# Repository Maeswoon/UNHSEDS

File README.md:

# UNH SEDS

This is the official GitHub for UNH Students for the Exploration and Development of Space. 

Every September and February, UNH SEDS will train members on the software needed to use this. 
This GitHub is purely used for versioning engineering files at the moment, although an archive
of previous years' files is kept for posterity.

Please contact Mason McDonald at mason.mcdonald@unh.edu to join! 

Let's get to work,

Mason McDonald
<br>
*President, UNH SEDS*

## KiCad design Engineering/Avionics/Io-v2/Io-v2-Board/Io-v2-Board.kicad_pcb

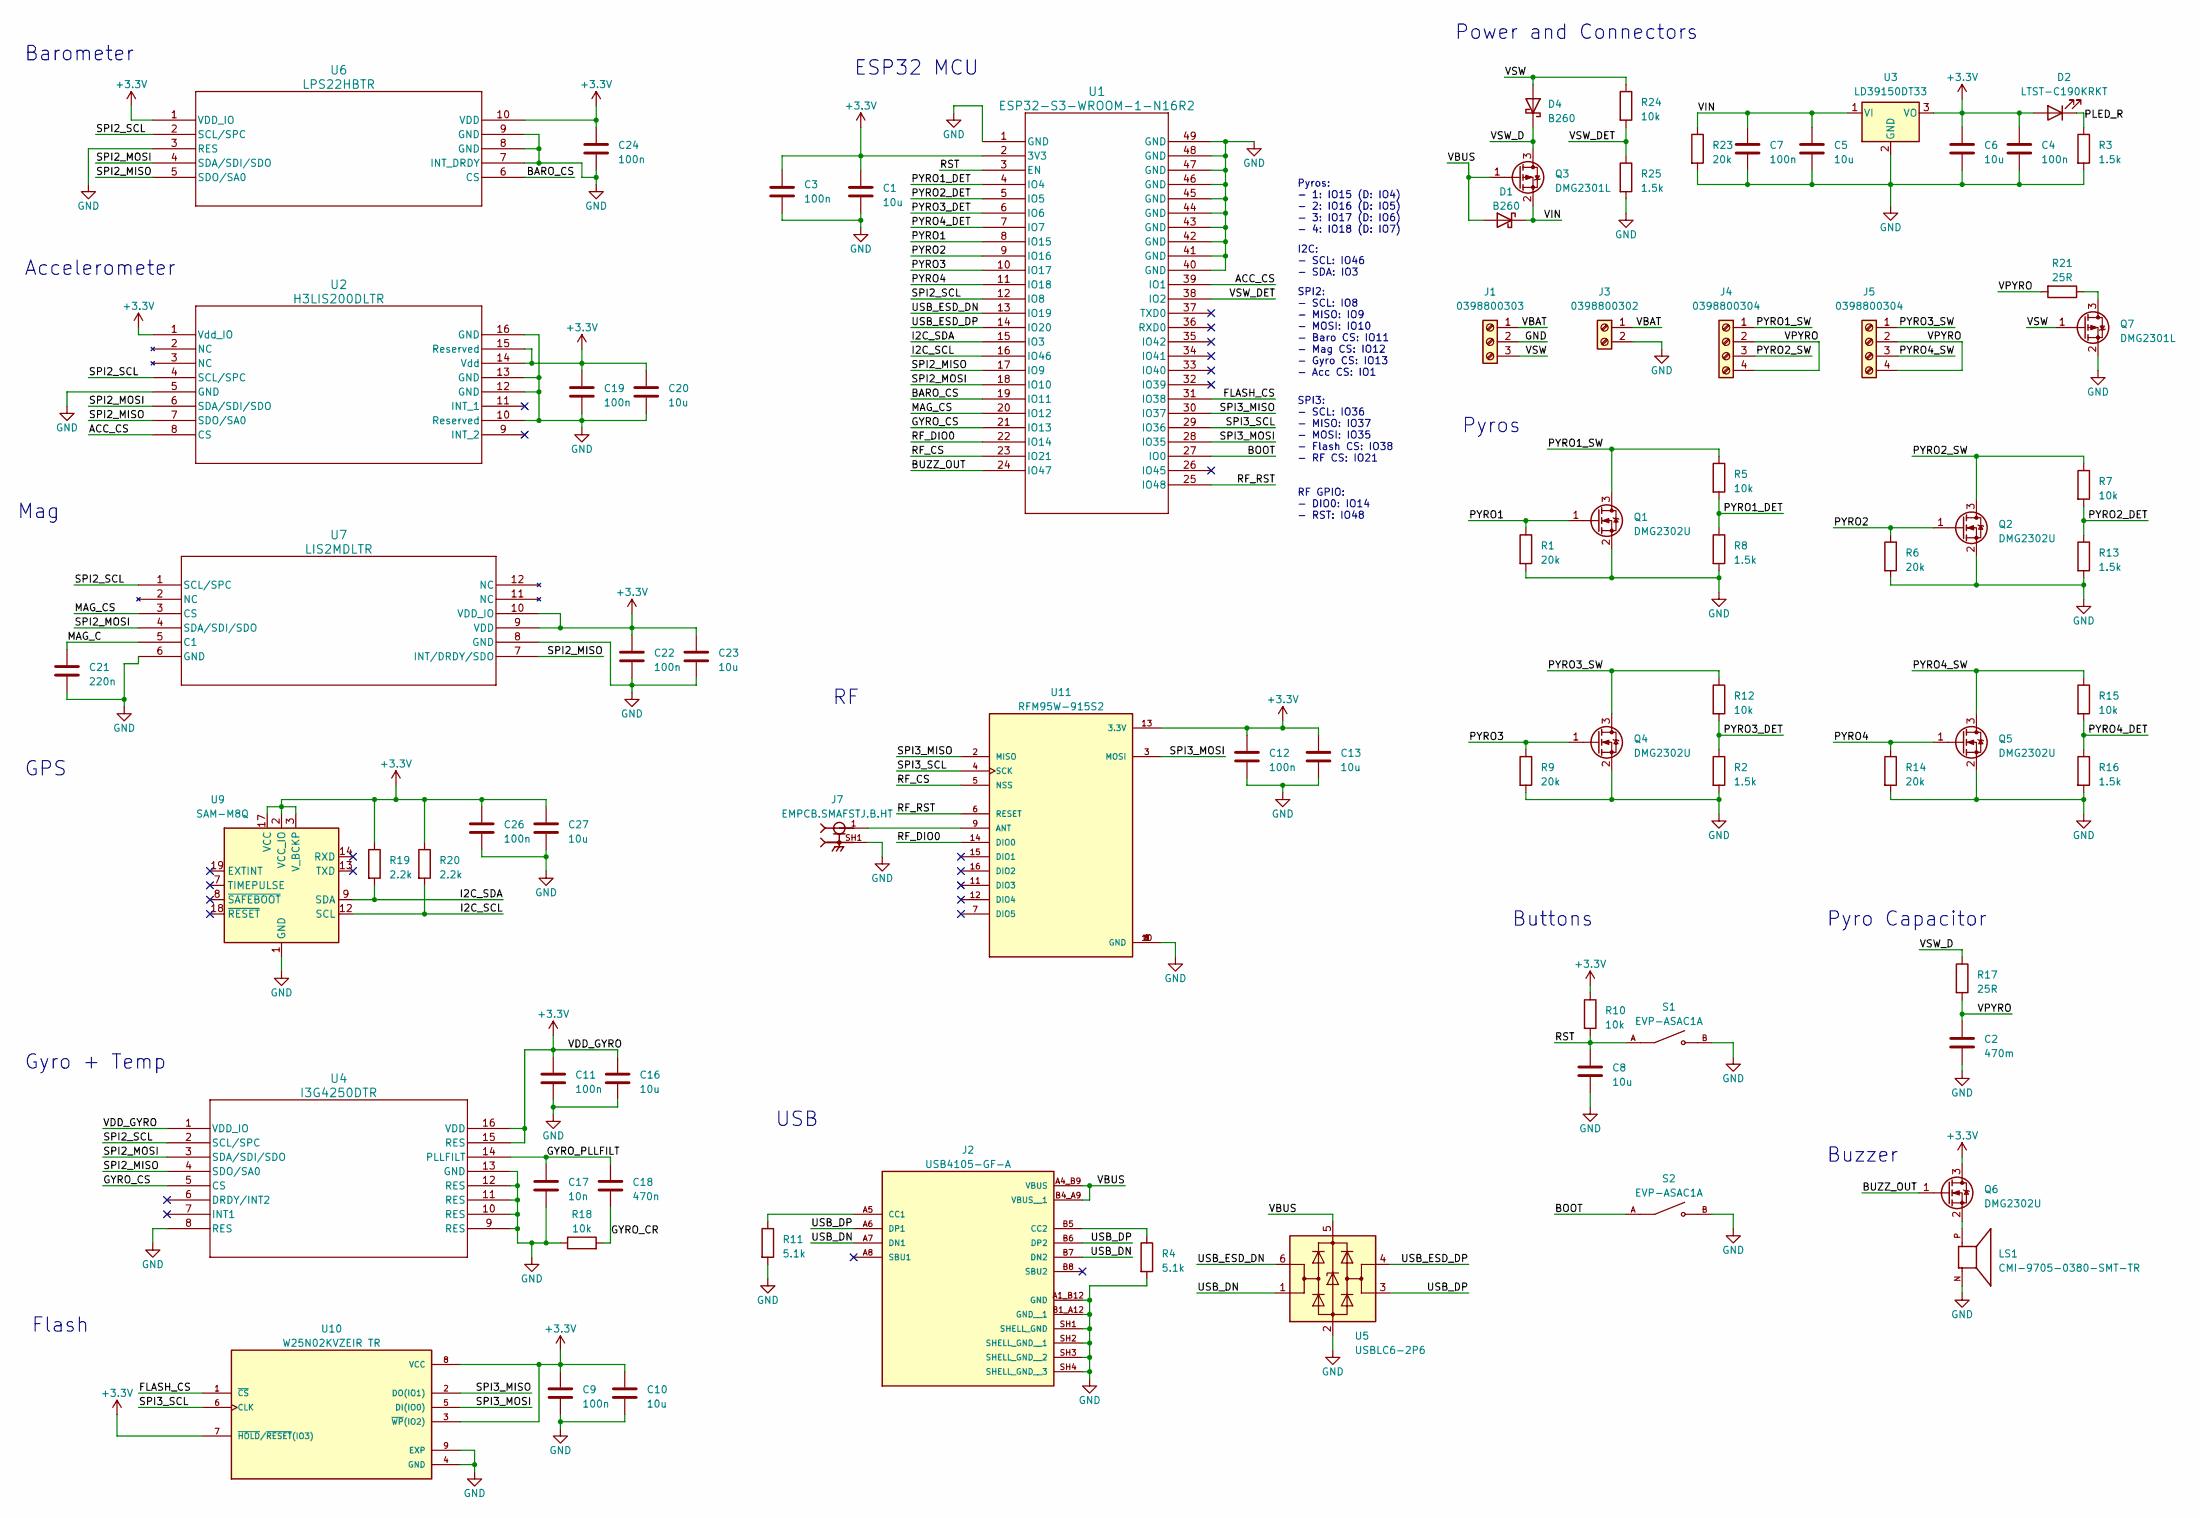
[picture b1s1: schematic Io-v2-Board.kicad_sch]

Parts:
C1, C5, C6, C8, C10, C13, C16, C20, C23, C27: 10u; C_0805_2012Metric
C2: 470m; PHV-5R4H474-R
C3, C4, C7, C9, C11, C12, C19, C22, C24, C26: 100n; C_0603_1608Metric
C17: 10n; C_0603_1608Metric
C18: 470n; C_0603_1608Metric
C21: 220n; C_0603_1608Metric
D1, D4: B260; D_SMB
D2: LTST-C190KRKT; LED_0603_1608Metric
J1: 0398800303
J2: USB4105-GF-A; GCT_USB4105-GF-A; PARTREV B3
J3: 0398800302
J4, J5: 0398800304
J7: EMPCB.SMAFSTJ.B.HT; TAOGLAS_EMPCB.SMAFSTJ.B.HT
LS1: CMI-9705-0380-SMT-TR; CUI_CMI-9705-0380-SMT-TR; PARTREV 1.0
Q1, Q2, Q4, Q5, Q6: DMG2302U; SOT-23
Q3, Q7: DMG2301L; SOT-23
R1, R6, R9, R14, R23: 20k; R_0402_1005Metric
R2, R3, R8, R13, R16, R25: 1.5k; R_0402_1005Metric
R4, R11: 5.1k; R_0402_1005Metric
R5, R7, R10, R12, R15, R18, R24: 10k; R_0402_1005Metric
R17, R21: 25R; R_0603_1608Metric
R19, R20: 2.2k; R_0402_1005Metric
S1, S2: EVP-ASAC1A; SW_EVP-ASAC1A; PARTREV 2022.4
U1: ESP32-S3-WROOM-1-N16R2; ESP32-S3-WROOM-1_EXP
U2: H3LIS200DLTR; TFLGA_S200DL_STM
U3: LD39150DT33; TO-252-3_TabPin2
U4: I3G4250DTR; LGA-16_4X4X1_STM
U5: USBLC6-2P6; SOT-666
U6: LPS22HBTR; HLGA10_2X2_STM
U7: LIS2MDLTR; LGA-12_2X2X1_STM
U9: SAM-M8Q; ublox_SAM-M8Q
U10: W25N02KVZEIR TR; WSON-8-1EP_8x6mm_P1.27mm_EP3.4x4.3mm; PARTREV G
U11: RFM95W-915S2

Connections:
+3.3V: C1.1, C3.1, C4.1, C6.1, C9.1, C10.1, C11.1, C12.1, C13.1, C16.1, C19.1, C20.1, C22.1, C23.1, C24.1, C26.1, C27.1, D2.2 (A), Q6.3 (D), R10.1, R19.1, R20.1, U1.2 (3V3), U2.1 (Vdd_IO), U2.14 (Vdd), U2.15 (Reserved), U3.3 (VO), U4.1 (VDD_IO), U4.15 (RES), U4.16 (VDD), U6.1 (VDD_IO), U6.10 (VDD), U7.9 (VDD), U7.10 (VDD_IO), U9.2 (VCC_IO), U9.3 (V_BCKP), U9.17 (VCC), U10.3 (~WP(IO2)), U10.7 (~HOLD/~RESET(IO3)), U10.8 (VCC), U11.13 (3.3V)
/ACC_CS: U1.39 (IO1), U2.8 (CS)
/BARO_CS: U1.19 (IO11), U6.6 (CS)
/BOOT: S2.A, U1.27 (IO0)
/BUZZ_OUT: Q6.1 (G), U1.24 (IO47)
/FLASH_CS: U1.31 (IO38), U10.1 (~CS)
/GYRO_CR: C18.2, R18.2
/GYRO_CS: U1.21 (IO13), U4.5 (CS)
/GYRO_PLLFILT: C17.1, C18.1, U4.14 (PLLFILT)
/I2C_SCL: R20.2, U1.16 (IO46), U9.12 (SCL)
/I2C_SDA: R19.2, U1.15 (IO3), U9.9 (SDA)
/MAG_C: C21.1, U7.5 (C1)
/MAG_CS: U1.20 (IO12), U7.3 (CS)
/PLED_R: D2.1 (K), R3.1
/PYRO1: Q1.1 (G), R1.1, U1.8 (IO15)
/PYRO1_DET: R5.2, R8.1, U1.4 (IO4)
/PYRO1_SW: J4.1, Q1.3 (D), R5.1
/PYRO2: Q2.1 (G), R6.1, U1.9 (IO16)
/PYRO2_DET: R7.2, R13.1, U1.5 (IO5)
/PYRO2_SW: J4.3, Q2.3 (D), R7.1
/PYRO3: Q4.1 (G), R9.1, U1.10 (IO17)
/PYRO3_DET: R2.1, R12.2, U1.6 (IO6)
/PYRO3_SW: J5.1, Q4.3 (D), R12.1
/PYRO4: Q5.1 (G), R14.1, U1.11 (IO18)
/PYRO4_DET: R15.2, R16.1, U1.7 (IO7)
/PYRO4_SW: J5.3, Q5.3 (D), R15.1
/RF_CS: U1.23 (IO21), U11.5 (NSS)
/RF_DIO0: U1.22 (IO14), U11.14 (DIO0)
/RF_RST: U1.25 (IO48), U11.6 (RESET)
/RST: C8.1, R10.2, S1.A, U1.3 (EN)
/SPI2_MISO: U1.17 (IO9), U2.7 (SDO/SA0), U4.4 (SDO/SA0), U6.5 (SDO/SA0), U7.7 (INT/DRDY/SDO)
/SPI2_MOSI: U1.18 (IO10), U2.6 (SDA/SDI/SDO), U4.3 (SDA/SDI/SDO), U6.4 (SDA/SDI/SDO), U7.4 (SDA/SDI/SDO)
/SPI2_SCL: U1.12 (IO8), U2.4 (SCL/SPC), U4.2 (SCL/SPC), U6.2 (SCL/SPC), U7.1 (SCL/SPC)
/SPI3_MISO: U1.30 (IO37), U10.2 (DO(IO1)), U11.2 (MISO)
/SPI3_MOSI: U1.28 (IO35), U10.5 (DI(IO0)), U11.3 (MOSI)
/SPI3_SCL: U1.29 (IO36), U10.6 (CLK), U11.4 (SCK)
/USB_DN: J2.A7 (DN1), J2.B7 (DN2), U5.1 (I/O1)
/USB_DP: J2.A6 (DP1), J2.B6 (DP2), U5.3 (I/O2)
/USB_ESD_DN: U1.13 (IO19), U5.6 (I/O1)
/USB_ESD_DP: U1.14 (IO20), U5.4 (I/O2)
/VBAT: J1.1, J3.1
/VBUS: D1.2 (A), J2.A4_B9 (VBUS), J2.B4_A9 (VBUS__1), Q3.1 (G), U5.5 (VBUS)
/VIN: C5.1, C7.1, D1.1 (K), Q3.2 (S), R23.1, U3.1 (VI)
/VPYRO: C2.1, J4.2, J4.4, J5.2, J5.4, R17.2, R21.2
/VSW: D4.2 (A), J1.3, Q7.1 (G), R24.1
/VSW_D: D4.1 (K), Q3.3 (D), R17.1
/VSW_DET: R24.2, R25.1, U1.38 (IO2)
GND: C1.2, C2.2, C3.2, C4.2, C5.2, C6.2, C7.2, C8.2, C9.2, C10.2, C11.2, C12.2, C13.2, C16.2, C17.2, C19.2, C20.2, C21.2, C22.2, C23.2, C24.2, C26.2, C27.2, J1.2, J2.A1_B12 (GND), J2.B1_A12 (GND__1), J2.SH1 (SHELL_GND), J2.SH2 (SHELL_GND__1), J2.SH3 (SHELL_GND__2), J2.SH4 (SHELL_GND__3), J3.2, J7.SH1, J7.SH2, J7.SH3, J7.SH4, LS1.N, Q1.2 (S), Q2.2 (S), Q4.2 (S), Q5.2 (S), Q7.2 (S), R1.2, R2.2, R3.2, R4.2, R6.2, R8.2, R9.2, R11.2, R13.2, R14.2, R16.2, R18.1, R23.2, R25.2, S1.B, S2.B, U1.1 (GND), U1.40 (GND), U1.41 (GND), U1.42 (GND), U1.43 (GND), U1.44 (GND), U1.45 (GND), U1.46 (GND), U1.47 (GND), U1.48 (GND), U1.49 (GND), U2.5 (GND), U2.10 (Reserved), U2.12 (GND), U2.13 (GND), U2.16 (GND), U3.2 (GND), U4.8 (RES), U4.9 (RES), U4.10 (RES), U4.11 (RES), U4.12 (RES), U4.13 (GND), U5.2 (GND), U6.3 (RES), U6.7 (INT_DRDY), U6.8 (GND), U6.9 (GND), U7.6 (GND), U7.8 (GND), U9.1 (GND), U9.4 (GND), U9.5 (GND), U9.6 (GND), U9.10 (GND), U9.11 (GND), U9.15 (GND), U9.16 (GND), U9.20 (GND), U10.4 (GND), U10.9 (EXP), U11.1 (GND), U11.8 (GND), U11.10 (GND)
unnamed: J2.A5 (CC1), R11.1
unnamed: J2.B5 (CC2), R4.1
unnamed: LS1.P, Q6.2 (S)
unnamed: Q7.3 (D), R21.1
unnamed: J7.1, U11.9 (ANT)

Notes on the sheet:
SPI2: - SCL: IO8 - MISO: IO9 - MOSI: IO10 - Baro CS: IO11 - Mag CS: IO12 - Gyro CS: IO13 - Acc CS: IO1
Flash
RF GPIO: - DIO0: IO14 - RST: IO48
Mag
GPS
Accelerometer
Pyros: - 1: IO15 (D: IO4) - 2: IO16 (D: IO5) - 3: IO17 (D: IO6) - 4: IO18 (D: IO7)
USB
Buttons
Pyro Capacitor
I2C: - SCL: IO46 - SDA: IO3
Buzzer
ESP32 MCU
SPI3: - SCL: IO36 - MISO: IO37 - MOSI: IO35 - Flash CS: IO38 - RF CS: IO21
Barometer
Power and Connectors
Pyros
Gyro + Temp

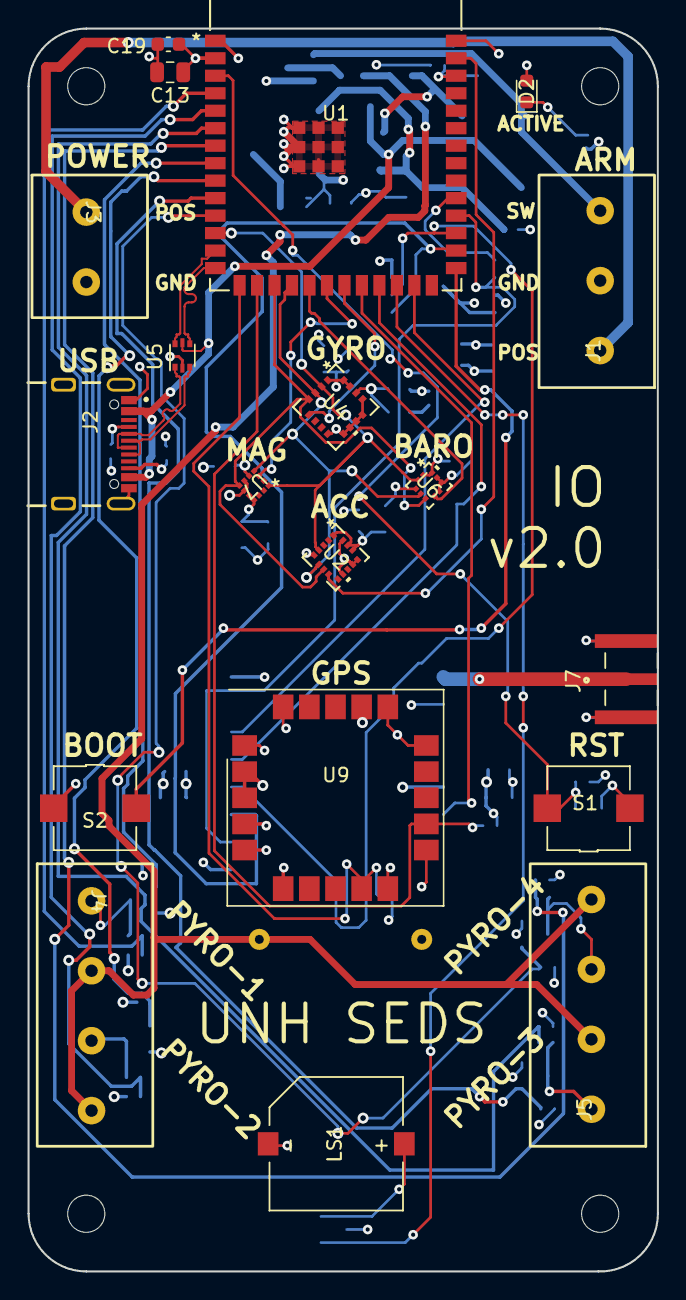
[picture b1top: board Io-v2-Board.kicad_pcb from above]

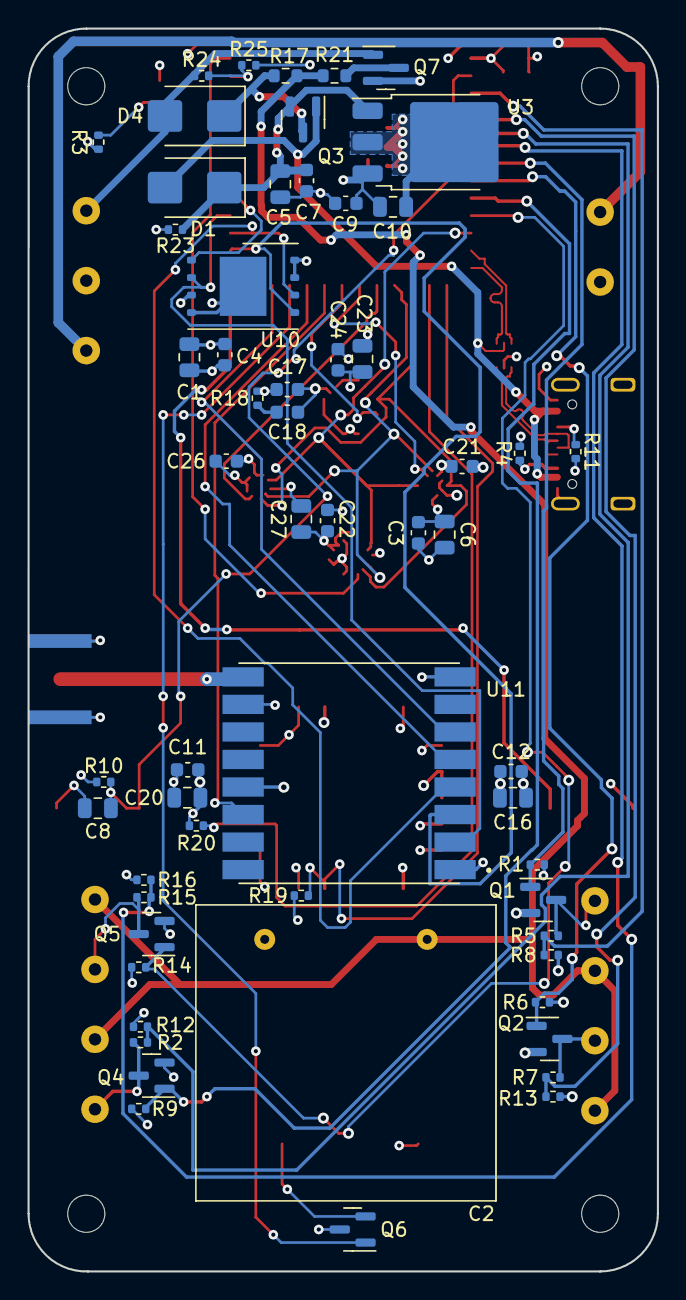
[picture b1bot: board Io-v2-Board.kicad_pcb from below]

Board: 4 copper layers, 45.7 x 90.3 mm, 81 parts (58 on the bottom side), 53 nets.

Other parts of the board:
H1, H2, H3, H4: MountingHole_2.7mm_M2.5_DIN965

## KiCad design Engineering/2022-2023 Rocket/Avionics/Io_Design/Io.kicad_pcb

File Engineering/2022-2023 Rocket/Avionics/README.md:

# Avionics TODO (version-to-version)

- More robust connectors
- Eliminate buck converter / diagnose ramp-up issue
- Add buzzer
- Ground connection for arming switch
- Reverse-voltage protection on pyros
- Integrated pyro resistors
- Neater PCB layout

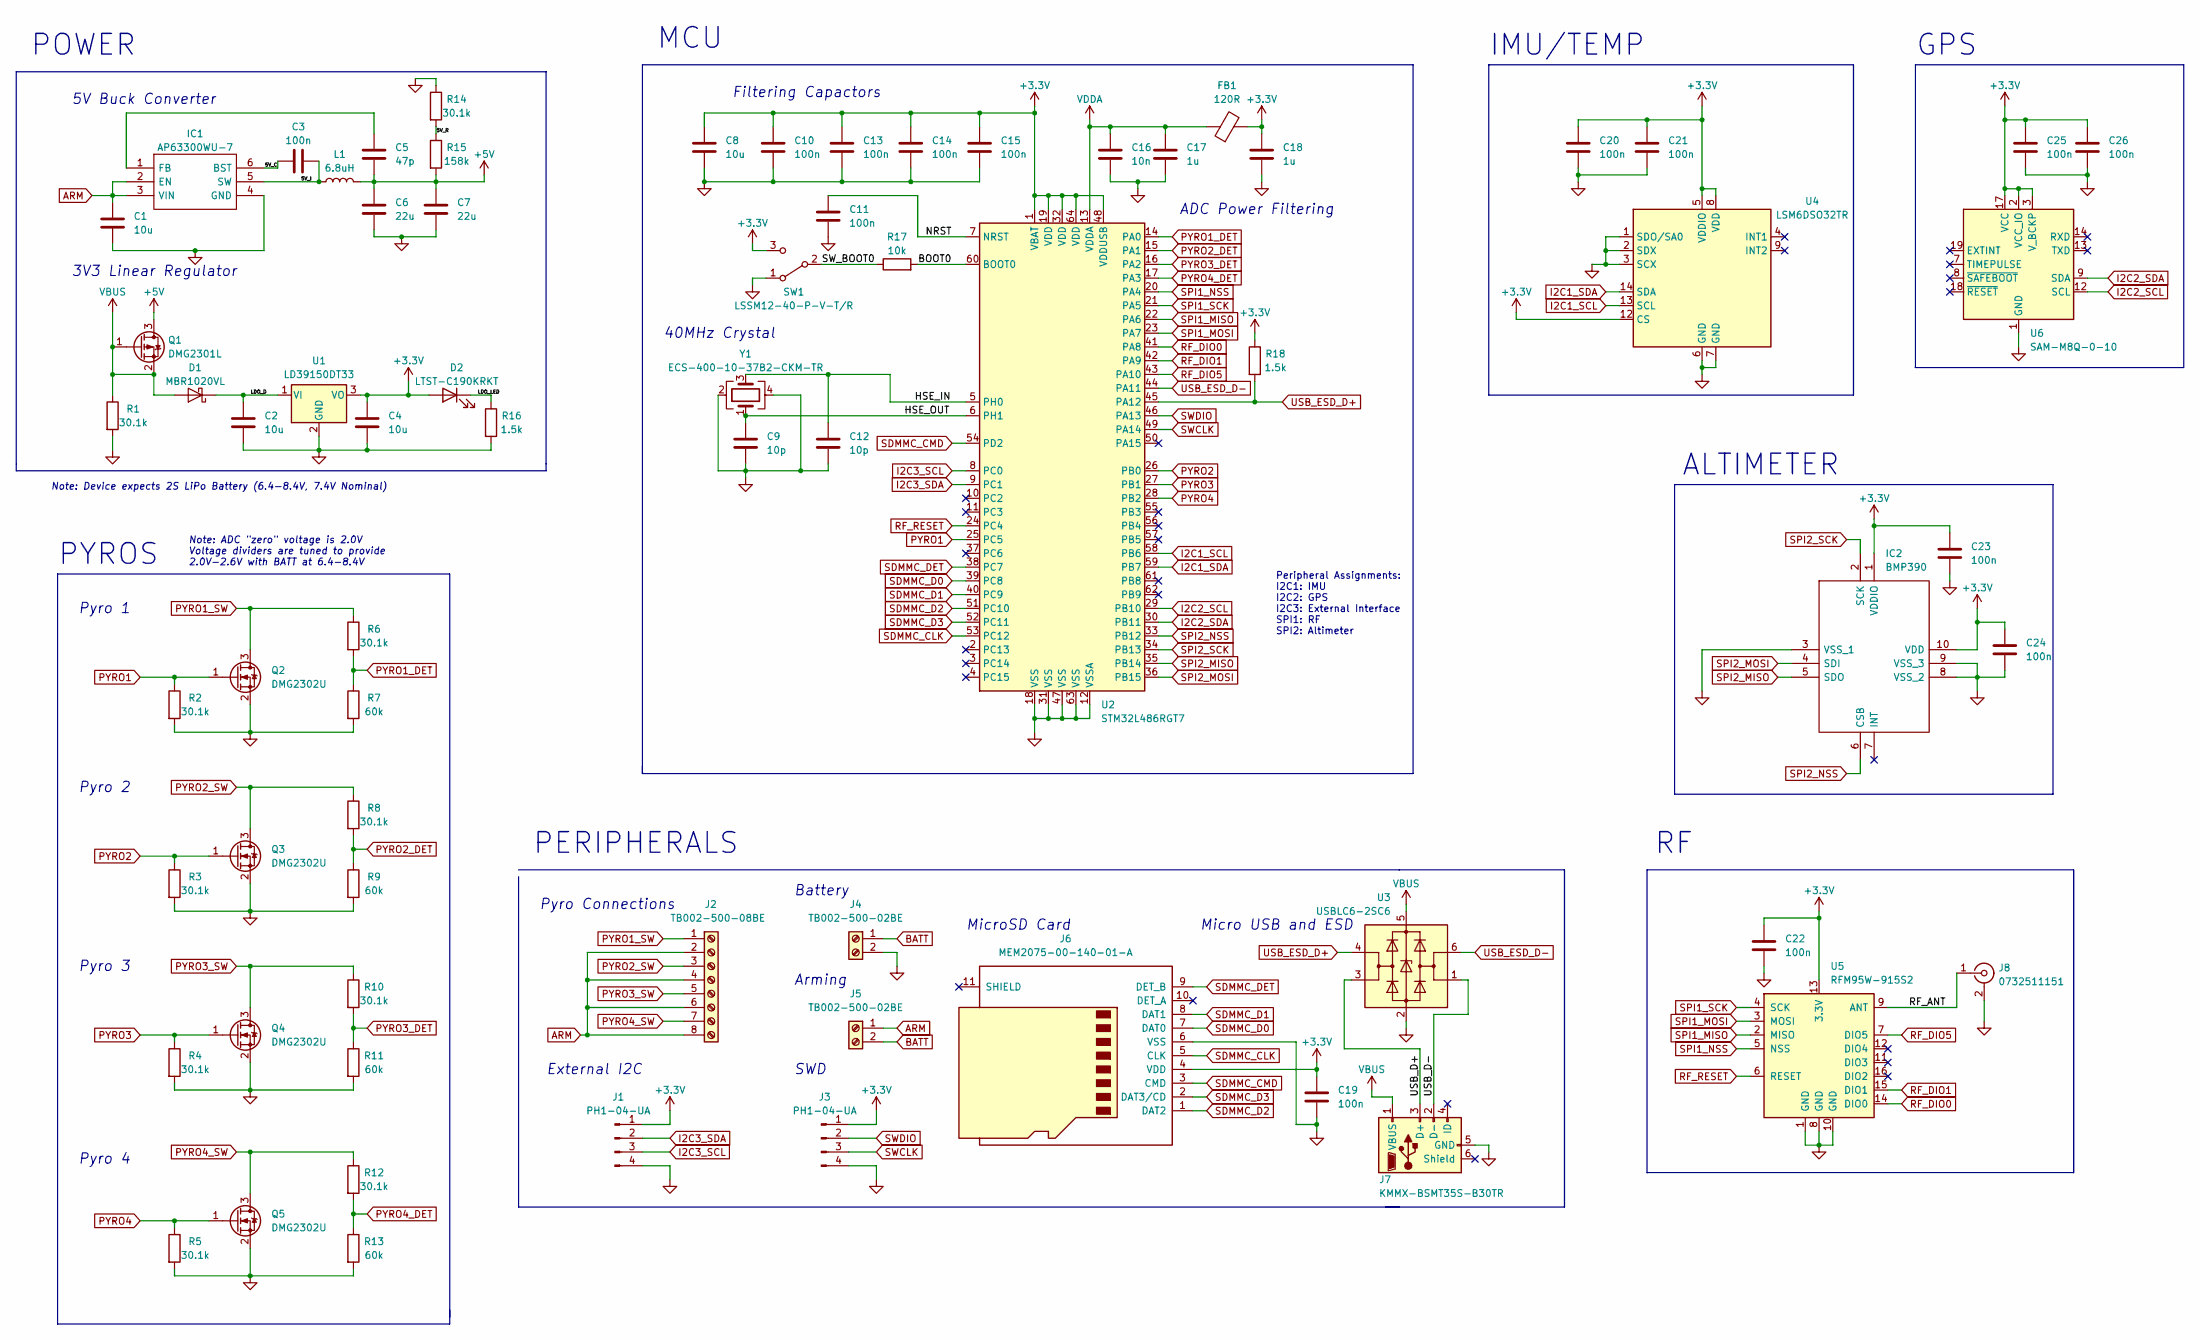
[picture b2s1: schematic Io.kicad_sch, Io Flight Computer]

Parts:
C1, C2, C4, C8: 10u; C_0603_1608Metric
C3, C10, C11, C13, C14, C15, C19, C20, C21, C22, C23, C24, C25, C26: 100n; C_0402_1005Metric
C5: 47p; C_0402_1005Metric
C6, C7: 22u; C_0603_1608Metric
C9, C12: 10p; C_0402_1005Metric
C16: 10n; C_0402_1005Metric
C17, C18: 1u; C_0402_1005Metric
D1: MBR1020VL; D_SOD-123F
D2: LTST-C190KRKT; LED_0603_1608Metric
FB1: 120R; L_0201_0603Metric
IC1: AP63300WU-7; TSOT-23-6; Mouser Part Number 621-AP63300WU-7
IC2: BMP390; Mouser Part Number 262-BMP390
J1, J3: PH1-04-UA; PinHeader_1x04_P2.54mm_Vertical
J2: TB002-500-08BE; TerminalBlock_TE_282834-8_1x08_P2.54mm_Horizontal
J4, J5: TB002-500-02BE; TerminalBlock_TE_282834-2_1x02_P2.54mm_Horizontal
J6: MEM2075-00-140-01-A
J7: KMMX-BSMT35S-B30TR; KMMXBSMT35SB30TR
J8: 0732511151; SMA_Molex_73251-1153_EdgeMount_Horizontal
L1: 6.8uH; L_Bourns_SRR1260
Q1: DMG2301L; SOT-23
Q2, Q3, Q4, Q5: DMG2302U; SOT-23
R1, R2, R3, R4, R5, R6, R8, R10, R12, R14: 30.1k; R_0402_1005Metric
R7, R9, R11, R13: 60k; R_0603_1608Metric
R15: 158k; R_0805_2012Metric
R16, R18: 1.5k; R_0402_1005Metric
R17: 10k; R_0402_1005Metric
SW1: LSSM12-40-P-V-T/R; LSSM1240PVTR
U1: LD39150DT33; TO-252-3_TabPin2
U2: STM32L486RGT7; LQFP-64_10x10mm_P0.5mm
U3: USBLC6-2SC6; SOT-23-6
U4: LSM6DSO32TR; LGA-14_3x2.5mm_P0.5mm_LayoutBorder3x4y
U5: RFM95W-915S2
U6: SAM-M8Q-0-10; ublox_SAM-M8Q
Y1: ECS-400-10-37B2-CKM-TR; Crystal_SMD_2016-4Pin_2.0x1.6mm

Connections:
+3.3V: C4.1, C8.1, C10.1, C13.1, C14.1, C15.1, C18.1, C19.1, C20.1, C21.1, C22.1, C23.1, C24.1, C25.1, C26.1, D2.2 (A), FB1.2, IC2.1 (VDDIO), IC2.10 (VDD), J1.1, J3.1, J6.4 (VDD), R18.1, SW1.3 (C), U1.3 (VO), U2.1 (VBAT), U2.19 (VDD), U2.32 (VDD), U2.48 (VDDUSB), U2.64 (VDD), U4.5 (VDDIO), U4.8 (VDD), U4.12 (CS), U5.13 (3.3V), U6.2 (VCC_IO), U6.3 (V_BCKP), U6.17 (VCC)
+5V: C5.2, C6.1, C7.1, L1.2, Q1.3 (D), R15.2
/5V_C: C3.2, IC1.6 (BST)
/5V_I: C3.1, IC1.5 (SW), L1.1
/5V_R: R14.2, R15.1
/BOOT0: R17.2, U2.60 (BOOT0)
/HSE_IN: C12.1, U2.5 (PH0), Y1.3
/HSE_OUT: C9.1, U2.6 (PH1), Y1.1
/LDO_D: C2.1, D1.1 (K), U1.1 (VI)
/LDO_LED: D2.1 (K), R16.1
/NRST: C11.1, U2.7 (NRST)
/RF_ANT: J8.1 (In), U5.9 (ANT)
/SW_BOOT0: R17.1, SW1.2 (B)
/USB_D+: J7.3 (D+), U3.3 (I/O2)
/USB_D-: J7.2 (D-), U3.1 (I/O1)
ARM: C1.1, IC1.2 (EN), IC1.3 (VIN), J2.2, J2.4, J2.6, J2.8, J5.1
BATT: J4.1, J5.2
GND: C1.2, C2.2, C4.2, C6.2, C7.2, C8.2, C9.2, C10.2, C11.2, C12.2, C13.2, C14.2, C15.2, C16.2, C17.2, C18.2, C19.2, C20.2, C21.2, C22.2, C23.2, C24.2, C25.2, C26.2, IC1.4 (GND), IC2.3 (VSS_1), IC2.8 (VSS_2), IC2.9 (VSS_3), J1.4, J3.4, J4.2, J6.6 (VSS), J7.5 (GND), J8.2 (Ext), Q2.2 (S), Q3.2 (S), Q4.2 (S), Q5.2 (S), R1.2, R2.2, R3.2, R4.2, R5.2, R7.2, R9.2, R11.2, R13.2, R14.1, R16.2, SW1.1 (A), U1.2 (GND), U2.12 (VSSA), U2.18 (VSS), U2.31 (VSS), U2.47 (VSS), U2.63 (VSS), U3.2 (GND), U4.1 (SDO/SA0), U4.2 (SDX), U4.3 (SCX), U4.6 (GND), U4.7 (GND), U5.1 (GND), U5.8 (GND), U5.10 (GND), U6.1 (GND), U6.4 (GND), U6.5 (GND), U6.6 (GND), U6.10 (GND), U6.11 (GND), U6.15 (GND), U6.16 (GND), U6.20 (GND), Y1.2, Y1.4; also elsewhere on the board
I2C1_SCL: U2.58 (PB6), U4.13 (SCL)
I2C1_SDA: U2.59 (PB7), U4.14 (SDA)
I2C2_SCL: U2.29 (PB10), U6.12 (SCL)
I2C2_SDA: U2.30 (PB11), U6.9 (SDA)
I2C3_SCL: J1.3, U2.8 (PC0)
I2C3_SDA: J1.2, U2.9 (PC1)
unnamed: C5.1, IC1.1 (FB)
PYRO1: Q2.1 (G), R2.1, U2.25 (PC5)
PYRO1_DET: R6.2, R7.1, U2.14 (PA0)
PYRO1_SW: J2.1, Q2.3 (D), R6.1
PYRO2: Q3.1 (G), R3.1, U2.26 (PB0)
PYRO2_DET: R8.2, R9.1, U2.15 (PA1)
PYRO2_SW: J2.3, Q3.3 (D), R8.1
PYRO3: Q4.1 (G), R4.1, U2.27 (PB1)
PYRO3_DET: R10.2, R11.1, U2.16 (PA2)
PYRO3_SW: J2.5, Q4.3 (D), R10.1
PYRO4: Q5.1 (G), R5.1, U2.28 (PB2)
PYRO4_DET: R12.2, R13.1, U2.17 (PA3)
PYRO4_SW: J2.7, Q5.3 (D), R12.1
RF_DIO0: U2.41 (PA8), U5.14 (DIO0)
RF_DIO1: U2.42 (PA9), U5.15 (DIO1)
RF_DIO5: U2.43 (PA10), U5.7 (DIO5)
RF_RESET: U2.24 (PC4), U5.6 (RESET)
SDMMC_CLK: J6.5 (CLK), U2.53 (PC12)
SDMMC_CMD: J6.3 (CMD), U2.54 (PD2)
SDMMC_D0: J6.7 (DAT0), U2.39 (PC8)
SDMMC_D1: J6.8 (DAT1), U2.40 (PC9)
SDMMC_D2: J6.1 (DAT2), U2.51 (PC10)
SDMMC_D3: J6.2 (DAT3/CD), U2.52 (PC11)
SDMMC_DET: J6.9 (DET_B), U2.38 (PC7)
SPI1_MISO: U2.22 (PA6), U5.2 (MISO)
SPI1_MOSI: U2.23 (PA7), U5.3 (MOSI)
SPI1_NSS: U2.20 (PA4), U5.5 (NSS)
SPI1_SCK: U2.21 (PA5), U5.4 (SCK)
SPI2_MISO: IC2.5 (SDO), U2.35 (PB14)
SPI2_MOSI: IC2.4 (SDI), U2.36 (PB15)
SPI2_NSS: IC2.6 (CSB), U2.33 (PB12)
SPI2_SCK: IC2.2 (SCK), U2.34 (PB13)
SWCLK: J3.3, U2.49 (PA14)
SWDIO: J3.2, U2.46 (PA13)
USB_ESD_D+: R18.2, U2.45 (PA12), U3.4 (I/O2)
USB_ESD_D-: U2.44 (PA11), U3.6 (I/O1)
VBUS: D1.2 (A), J7.1 (VBUS), Q1.1 (G), Q1.2 (S), R1.1, U3.5 (VBUS)
VDDA: C16.1, C17.1, FB1.1, U2.13 (VDDA)

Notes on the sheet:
Battery
Pyro Connections
Pyro 2
3V3 Linear Regulator
Filtering Capactors
5V Buck Converter
MicroSD Card
Micro USB and ESD
Pyro 1
MCU
PYROS
ADC Power Filtering
ALTIMETER
40MHz Crystal
GPS
Arming
PERIPHERALS
Peripheral Assignments: I2C1: IMU I2C2: GPS I2C3: External Interface SPI1: RF SPI2: Altimeter
Pyro 3
Note: ADC "zero" voltage is 2.0V Voltage dividers are tuned to provide 2.0V-2.6V with BATT at 6.4-8.4V
Note: Device expects 2S LiPo Battery (6.4-8.4V, 7.4V Nominal)
External I2C
POWER
IMU/TEMP
Pyro 4
SWD

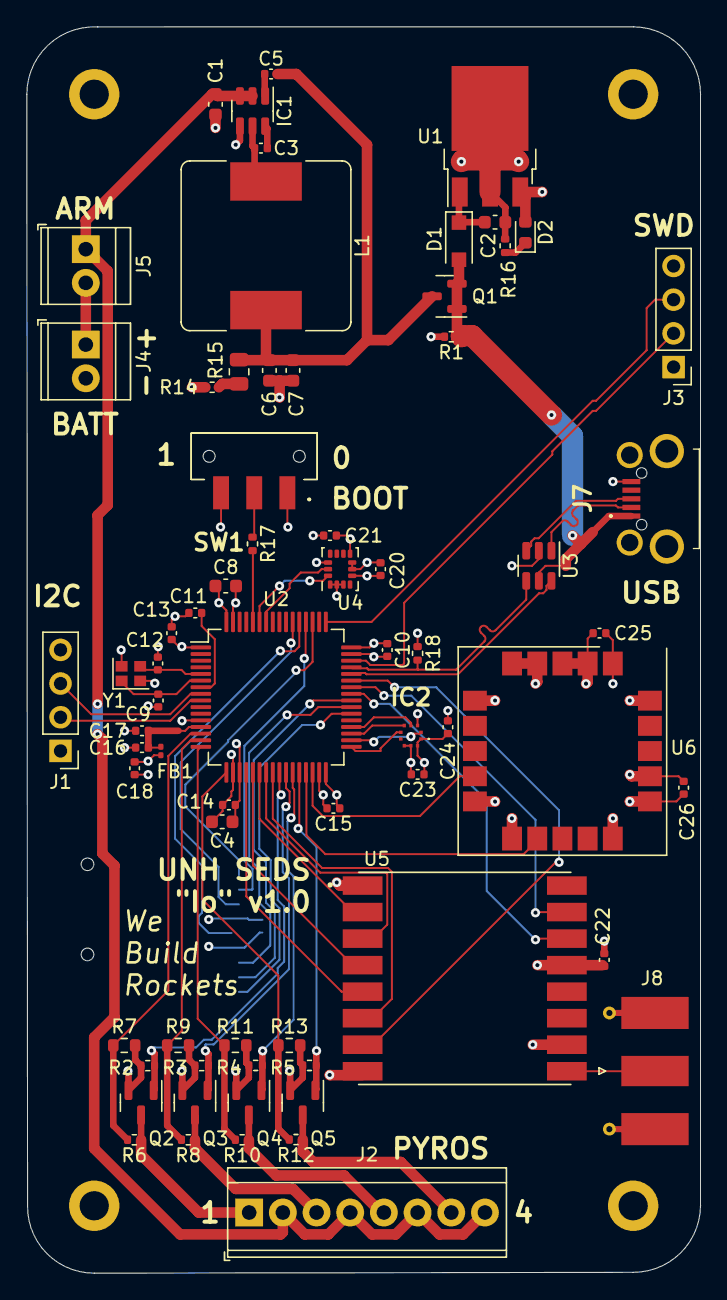
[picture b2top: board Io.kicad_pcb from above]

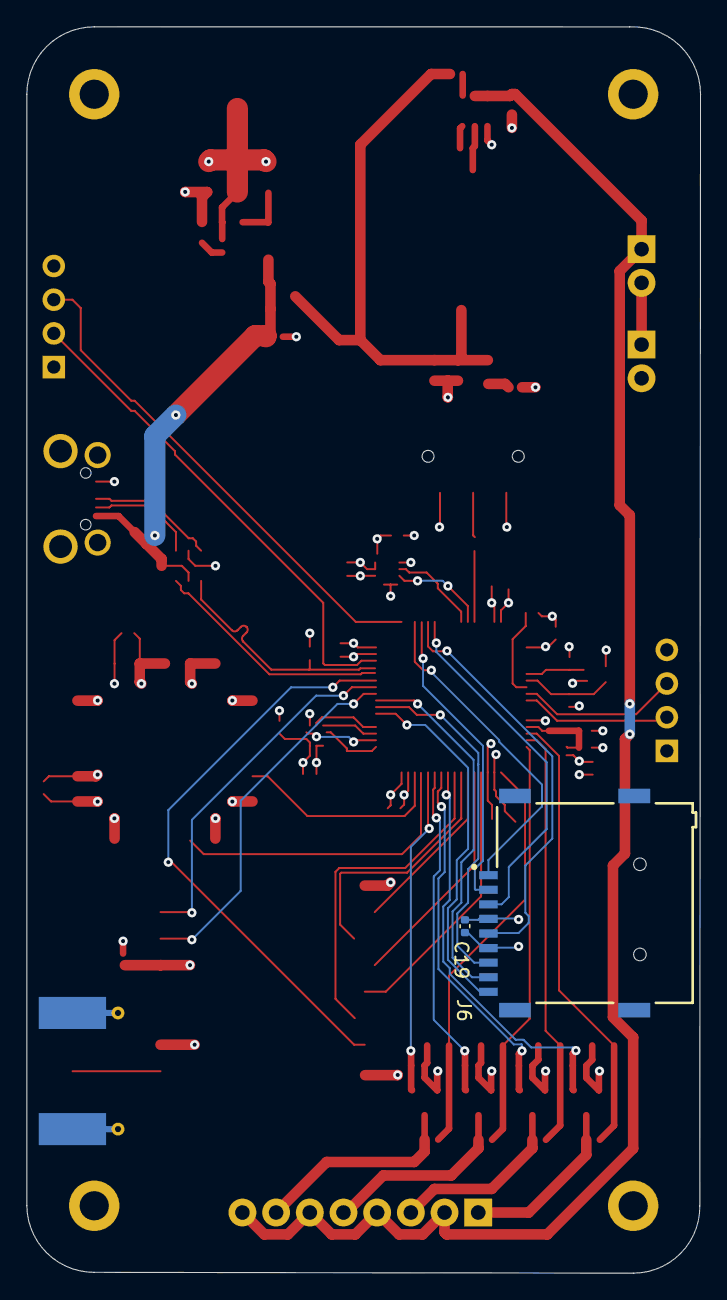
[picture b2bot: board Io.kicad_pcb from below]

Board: 4 copper layers, 50.8 x 94.0 mm, 75 parts (2 on the bottom side), 62 nets.

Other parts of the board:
H1, H2, H3, H4: MountingHole_2.2mm_M2_DIN965_Pad

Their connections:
GND: H1.1, H2.1, H3.1, H4.1; also elsewhere on the board

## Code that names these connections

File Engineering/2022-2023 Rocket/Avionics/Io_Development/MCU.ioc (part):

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Mcu.Name=STM32L486RGTx
Mcu.Package=LQFP64
Mcu.UserName=STM32L486RGTx
PA0.GPIOParameters=GPIO_Label
PA0.GPIO_Label=PYRO1_DET
PA0.Signal=ADCx_IN5
PA1.GPIOParameters=GPIO_Label
PA1.GPIO_Label=PYRO2_DET
PA1.Signal=ADCx_IN6
PA10.GPIOParameters=GPIO_Label
PA10.GPIO_Label=RF_DIO5
PA10.Signal=GPIO_Input
PA11.Mode=Device_Only
PA11.Signal=USB_OTG_FS_DM
PA12.GPIOParameters=GPIO_Label
PA12.GPIO_Label=USB_OTG_FS_DP
PA12.Mode=Device_Only
PA12.Signal=USB_OTG_FS_DP
PA13\ (JTMS-SWDIO).Mode=Serial_Wire
PA13\ (JTMS-SWDIO).Signal=SYS_JTMS-SWDIO
PA14\ (JTCK-SWCLK).Mode=Serial_Wire
PA14\ (JTCK-SWCLK).Signal=SYS_JTCK-SWCLK
PA2.GPIOParameters=GPIO_Label
PA2.GPIO_Label=PYRO3_DET
PA2.Signal=ADCx_IN7
PA3.GPIOParameters=GPIO_Label
PA3.GPIO_Label=PYRO4_DET
PA3.Signal=ADCx_IN8
PA4.Mode=NSS_Signal_Hard_Output
PA4.Signal=SPI1_NSS
PA5.Mode=Full_Duplex_Master
PA5.Signal=SPI1_SCK
PA6.Mode=Full_Duplex_Master
PA6.Signal=SPI1_MISO
PA7.Mode=Full_Duplex_Master
PA7.Signal=SPI1_MOSI
PA8.GPIOParameters=GPIO_Label
PA8.GPIO_Label=RF_DIO0
PA8.Signal=GPIO_Input
PA9.GPIOParameters=GPIO_Label
PA9.GPIO_Label=RF_DIO1
PA9.Signal=GPIO_Input
PB0.GPIOParameters=GPIO_PuPd,GPIO_Label
PB0.GPIO_Label=PYRO2
PB0.GPIO_PuPd=GPIO_PULLDOWN
PB0.Signal=GPIO_Output
PB1.GPIOParameters=GPIO_PuPd,GPIO_Label
PB1.GPIO_Label=PYRO3
PB1.GPIO_PuPd=GPIO_PULLDOWN
PB1.Signal=GPIO_Output
PB10.Mode=I2C
PB10.Signal=I2C2_SCL
PB11.Mode=I2C
PB11.Signal=I2C2_SDA
PB12.Mode=NSS_Signal_Hard_Output
PB12.Signal=SPI2_NSS
PB13.Mode=Full_Duplex_Master
PB13.Signal=SPI2_SCK
PB14.Mode=Full_Duplex_Master
PB14.Signal=SPI2_MISO
PB15.Mode=Full_Duplex_Master
PB15.Signal=SPI2_MOSI
PB2.GPIOParameters=GPIO_PuPd,GPIO_Label
PB2.GPIO_Label=PYRO4
PB2.GPIO_PuPd=GPIO_PULLDOWN
PB2.Signal=GPIO_Output
PB6.Mode=I2C
PB6.Signal=I2C1_SCL
PB7.Mode=I2C
PB7.Signal=I2C1_SDA
PC1.Mode=Half_duplex(single_wire_mode)
PC1.Signal=LPUART1_TX
PC10.Mode=SD_4_bits_Wide_bus
PC10.Signal=SDMMC1_D2
PC11.Mode=SD_4_bits_Wide_bus
PC11.Signal=SDMMC1_D3
PC12.Mode=SD_4_bits_Wide_bus
PC12.Signal=SDMMC1_CK
PC4.Signal=GPIO_Output
PC5.GPIOParameters=GPIO_PuPd,GPIO_Label
PC5.GPIO_Label=PYRO1
PC5.GPIO_PuPd=GPIO_PULLDOWN
PC5.Signal=GPIO_Output
PC7.GPIOParameters=GPIO_PuPd,GPIO_Label
PC7.GPIO_Label=SDMMC1_DET
PC7.GPIO_PuPd=GPIO_NOPULL
PC7.Signal=GPIO_Input
PC8.Mode=SD_4_bits_Wide_bus
PC8.Signal=SDMMC1_D0
PC9.Mode=SD_4_bits_Wide_bus
PC9.Signal=SDMMC1_D1
PD2.Mode=SD_4_bits_Wide_bus
PD2.Signal=SDMMC1_CMD
PH0-OSC_IN\ (PH0).Mode=HSE-External-Oscillator
PH0-OSC_IN\ (PH0).Signal=RCC_OSC_IN
PH1-OSC_OUT\ (PH1).Mode=HSE-External-Oscillator
PH1-OSC_OUT\ (PH1).Signal=RCC_OSC_OUT
RCC.HSE_VALUE=40000000
RCC.SYSCLKFreq_VALUE=80000000
RCC.SYSCLKSource=RCC_SYSCLKSOURCE_PLLCLK
board=custom

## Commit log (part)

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2020-03-04 yoyoyo
2020-03-04 ijuw9erj9
2020-03-05 Removed files longer than 260 charnames
2020-03-05 model updates
2020-03-05 frame
2020-03-05 yeet
2020-03-07 Updated recovery plate to .5 inch thickness and larger U-Bolts
2020-03-07 FEA for the recovery plate U-bolt and 6-32 bolts.
2020-03-07 43gg4w
2020-03-07 o8iyfot7g
2020-03-09 rail
2020-03-09 rail button model updates
2020-03-09 New IMping
2020-03-09 Ne plate
2020-03-09 Added fin and holder assembly
2020-03-09 Added test fin to main assembly
2020-03-09 Rocket Analysis
2020-03-09 rqwerq
2020-03-09 Added Fin models
2020-03-10 dRAWINGS
2020-03-10 darw
2020-03-10 ufisedu
2020-03-10 Meep
2020-03-10 Nice
2020-03-13 more plates
2020-04-01 none
2020-04-07 ywwt
2020-04-14 nothing
2020-04-22 pics
2020-04-24 hotfire
2020-04-24 none
    none
2020-07-29 Create Charlie Vomit
2020-07-29 Create Who Knows
2020-07-29 Orginization
    yeet
2020-08-20 Filepath Updates
2020-09-18 Updating Old Solidworks Files to New Solidworks
2020-09-25 Moving to 2020-2021 folder and rough modeling swirl injector system
2020-09-29 Moving Files
2020-09-30 Budget
2020-09-30 Cleaning
2020-09-30 Swirl Injector
2020-10-08 Banshee V1
2020-10-12 Swirl Injection System
2020-10-12 Backup initial commit
2020-10-12 Create autobackup.yml
    First test of the backup system
2020-10-12 Enable workflow?
2020-10-12 Rename autobackup.yml to backup.yml
2020-10-19 payload
2020-10-25 OpenRocket model of existing rocket
2020-10-25 moved file
2020-10-25 helllo
2020-10-25 uh oh
2020-10-28 Added .yml file to trigger daily backups
2020-10-28 Banshee Flow Simulation
2020-10-29 Banshee V1 w/ Fused Quartz Insert and Fuel
2020-11-03 11/3
2020-11-03 Chamber updates
2020-11-08 Renamed long files
2020-11-09 11/8
2020-11-12 Injection System Updates
2020-11-13 Oxidizer Flow Simulations
2020-11-14 Added new engine file, WIP version of new rocket
2020-11-15 Frame Attempt
2020-11-15 Engine update - still based on guesswork
2020-11-15 Modified gitignore to ignore temp files (will not affect temp files already in repo)
2020-11-15 Suppressed Files
2020-11-16 Exploded View
2020-11-20 Added flipped NOS Openrocket model
2020-11-21 Grace Alternate Design
2020-11-22 Added new coupler design
2020-11-23 Redid frame coupler design, still checking effectiveness
2020-11-24 added placeholder payload
2020-11-24 Finished new coupler design
2020-11-24 Alternative Frame Design Refined
2020-11-24 Revert "Finished new coupler design"
    This reverts commit a7b2bcf52f03682dffc53320e57199f14b449c5c.
    Unfuck grace/my merge
2020-11-24 Revert "Redid frame coupler design, still checking effectiveness"
    This reverts commit bca682a15d1be5d211a9640f86429e38745c3809.
    as above
2020-11-24 Revert "Added new coupler design"
    This reverts commit 3546c552df17cca951d07fd456a30e03a0c089d3.
    as above
2020-11-24 Refined Frame
2020-11-24 Redid new frame design, ready for Sunday
2020-11-25 Revised new coupler assembly
2020-11-29 Modified the new coupler based on Grace's feedback
2020-11-29 Added exploded view to frame V3
2020-12-01 Flow Simulations and Comparisons
2020-12-02 Shortened Coupler (Grace's Design)
2020-12-02 Added Kangli Folder
2020-12-03 Oxidizer Injection Simulations
2020-12-05 heat
2020-12-06 moar heat
2020-12-08 Oxidizer Simulations Complete
2020-12-09 Flow stuffs
2020-12-09 Final Flow Calc
2020-12-11 First Draft of the Final Frame Design (Needs Optimization)
2021-01-09 most recent
2021-01-14 Updating Graphite Inserts
2021-01-29 Updating screws to 10-32 for a FOS of 3.2
2021-02-02 Creating Drawing for Combustion System
2021-02-04 Initial Drawing PDF
2021-02-08 Frame Reduction and FOS
    Look at SIMULATIONS -> Optimization V2 -> Active Frame V2 -> Active Frame V2 AlumOpt and Avtice Framve V2 AlumOpt2
2021-02-09 DrawingsMM-->In
2021-02-11 Alum Frame Screw Hole Sizes
2021-02-21 Added screws to assembly
2021-02-22 Changing Graphite sizes for machining
2021-03-05 3/5 Drawings Update
2021-03-16 Gimbal assembly and parts
2021-03-18 Tolerance Update 3/18
2021-03-18 Adding Tolerance Class II fit to injector
2021-03-18 Adding injector port too
2021-03-18 Updated Drawings w/ Tolerances
2021-03-19 rhjtrr
2021-03-23 3/23
2021-03-24 Thermal Sim
    Thermal Simulation Files
2021-03-28 Updating Assembly w New Insulation
2021-03-29 asdf
    asdf
2021-03-29 NEW MARCH
    BAD LARRY
2021-03-29 Update
    er
2021-03-29 New Combustion Chamber Geometry
2021-03-29 Redid nozzle and injector
2021-04-01 700 PSI rated Chamber
2021-04-01 Revert "Revert "700 PSI rated Chamber""
    This reverts commit a690d4d72faa396d0ad42c5a72117073b7279554.
2021-04-01 asd
    asd
2021-04-01 Updating Prop Drawings
2021-04-02 sdf
    sdf
2021-04-05 New Sim 3
    3
2021-04-06 big boy
    asd
2021-04-06 sdf
    sdfg
2021-04-11 NozzleAdapterUpdates/Drawing
2021-04-17 New Assembly w/ Easily Machinable Combustion Chamber
2021-04-22 Easily Machineable System Drawings
2021-04-23 Renders
2021-05-12 clearing out sterf
2021-05-14 6i786uuyyd
2021-06-20 Organizing 1
2021-06-20 Organizing 2
2021-06-20 Organizing 3
2021-06-20 Organizing 4
2021-06-20 Organizing 5
2021-06-20 Organizing 6
2021-06-20 Organizing 7
2021-06-20 Organizing 8
2021-06-30 Updates 6/30
2021-06-30 Updating Shop Computer
2021-06-30 Updating Shop Computer 2
2021-06-30 Updating Shop Computer 3
2021-06-30 Updating Shop Computer 4
2021-06-30 Updating Shop Computer 5
2021-09-27 Added new folder for the new year, moved all the 2021 stuff over. Started cleaning up frame mess.
2021-09-27 Added new year folder, started cleaning up frame
2021-09-28 Added frame drawings
2021-10-02 More cleanup, removed a lot of old design study files and STLs. Parts are all there if we need to recreate them.
2021-10-08 Some frame stress sims, a little cleanup
2021-10-10 Redid internal frame in preparation for machining
2021-10-17 Added more guide parts, updated openrocket engine
2021-10-20 Added recovery plate
2021-11-17 Renamed rocket, frame folders
2021-11-17 Cleaned up folder structure, added Alex's spacer
2021-11-19 Revert "merge with remote"
    This reverts commit fca2d8e6741030dc038f4086bfdff9b68113572c.
2021-11-23 Moved a few missing files to this year's frame
2021-12-12 Redid several couplers to better fit NOS tank
2021-12-12 Modified nose cone to add frame insert
2021-12-17 Added fins to rocket assembly
2022-01-13 Added many guides, aluminum nose cone tip, new fin holder design
2022-01-13 Parafin Changes
2022-01-31 Design Adjustments
2022-02-09 New Nozzle
2022-02-10 MORE NOZZLE
2022-02-24 fixed NOS plate thickness
2022-02-25 Nozzle thermal analysis
2022-02-25 Removed large result files
2022-03-10 Create Banshee V2 Step Down
2022-03-29 Spacer, OpenRocket files
2022-04-01 Updated coupler drawings
2022-04-06 Create Dummy Payload Fixture.SLDPRT
    Payload fixture
2022-04-06 Redid payload/avionics bays, added many small parts
2022-04-11 Updated prop assembly
2022-04-11 Added misc parts, dummy new valve
2022-04-11 Replaced base plate, fixed valve plate
2022-04-12 added nozzle base drawing
2022-04-12 Ababa
2022-04-12 Render Changes
2022-04-12 Render2
2022-04-12 Small updates to fit CC plates
2022-04-13 Updated valve plate
2022-04-14 Updated nozzle base drawing
2022-04-15 Added wide-tolerance nozzle base for 3d printing
2022-04-29 quick updates to assembly
2022-05-19 Last bits, OpenRocket update
2022-06-16 Reorganized for next year
2022-10-11 New Engine Rough Draft
2022-10-14 Open Rocket start
2022-10-17 Frame Components and Rocket Assembly
2022-11-10 updated engine model to use old nozzle
2022-11-16 Frame Assembly
2022-11-21 Engine bolt patter
2022-11-21 added oxidizer plate compatibility
2022-11-29 uwwertrw
2022-11-30 engine go brrr
2022-11-30 engine go brr
2022-11-30 engine go even more brrr
2022-12-25 Added Avionics schematics
2023-01-10 rutyde
2023-01-18 Updated Frame Rocket Assembly
    V2 of rocket assembly
2023-01-24 Avionics MCU switched to STM32
2023-01-25 Added 5V Regulator to schematic
2023-01-27 Added STM32 development code and power supply
2023-01-28 hgfhidfg
2023-01-30 engine update
2023-02-04 Finished schematic
2023-02-04 Schematic adjustments
2023-02-10 full asem 2
2023-02-10 Assem full 3
2023-02-10 Final test Assem
2023-02-16 Nozzle and engine coupler
2023-02-17 Started PCB design
2023-02-17 added wax to engine model
2023-02-17 engine rebuild
2023-02-22 fixed bolt pattern
2023-02-22 Fins and Hole tool
2023-02-22 FileLocateChange,FinHoleTool
2023-02-26 Major engine changes
2023-02-26 more engine changes and forgotten details
2023-02-28 Intermediate avionics update
2023-02-28 Lots of stuff
    Assembly update, alignment fixes, folder organization
2023-03-01 First PCB draft done. p a i n
2023-03-01 sdfhwsdfg
2023-03-02 Create Fin Spacer.SLDPRT
    Attempt at a fin spacer. Information on fin dimensions is needed to determine proper dimensions for spacer (especially circumference).
2023-03-03 Coupler and material edit
2023-03-05 Final engine
2023-03-05 added pressure tap holes
2023-03-06 Engine fix
2023-03-06 Created drawing for tapping specs
2023-03-06 o ring changes
2023-03-07 threads
2023-03-07 thread finalization
2023-03-08 drawing finalization
2023-03-10 Fin Holder Push
    Uploaded bracket to be printed four times to hold fins in place during attachment to rocket. Designed by Anthony, refined and updated by me.
2023-03-12 Redesigned with 4-layer board
2023-03-12 Alignment tools update
2023-03-12 Started avbay work
2023-03-12 Assem Update
2023-03-12 Avbay drafted
2023-03-12 AvBay assembly now 30% less sus
2023-03-13 assem update2
2023-03-13 Fixed AvBay sled
2023-03-14 Updated avbay sled for M3 inserts
2023-03-14 Added proposed bulkhead
2023-03-19 test
2023-03-21 thread confirmation
2023-03-22 Nosecone and tip changes
2023-03-22 Impinging plate updates for frame
2023-03-22 Impinging plate drawing change
2023-03-23 Nozzle Coupler
2023-03-23 impinging plate
2023-03-23 Prop Folder
2023-03-23 Please don't fuck the git up
2023-03-23 Assembly Fixes
2023-03-23 Why no work
2023-03-23 Create Solidworks
2023-03-23 Bolt Pattern Fixes
2023-03-23 tap updates
2023-03-23 taps
2023-03-23 Nozzle Drawing
2023-03-24 removed wrong oring and crew models for engine
2023-03-24 Fin, Engine coupler, Fin alignment updates
2023-03-24 payload assembly fix
2023-03-24 Finalized PCB design
2023-03-27 hole Alignment stuff
2023-03-27 final check
2023-03-28 payload assem, noz coupler
2023-03-28 Payload Bay
2023-03-28 fin slots and payload
2023-03-28 Bulkhead Update
2023-03-29 new impinging plate
2023-03-30 insulation and nose cone
2023-03-30 Recovery plate for raptor system and u-hooks
    solidworks part and .stl files
2023-03-31 Updated single bulkhead design
2023-03-31 Sims
2023-03-31 nosecone tip holder
2023-04-01 top hole allign
2023-04-01 Updated AvBay
2023-04-04 o ring groove tolerance fix
2023-04-05 Coupler stl and fins
2023-04-05 fin fillet
2023-04-07 Pipe Fittings
2023-04-11 Model Changes
2023-04-11 Render Updates
2023-04-11 old nosecone
2023-04-11 Changed Impinging plate
2023-04-14 Updated development files
2023-04-15 Updated avionics
2023-04-28 Final impinging plate
2023-05-03 o ring
2023-05-04 finalization check
2023-05-05 drawing
2023-05-16 materials
2023-07-13 Reorganized files for AY2023-2024
2023-07-13 Added concept designs
2023-07-16 Fixing up nozzle
2023-07-17 Converted back to safe casing thickness, finalized tentative dimensions, and added part drawings
2023-07-17 Added HRAP simulation config
2023-07-19 Final commit before review
2023-07-20 Tentative final concept revision
2023-09-26 Updated Concept designs
2023-10-10 Updated with new insulation and tapers
2023-10-10 Fixed bulkhead dimensions
2023-11-05 Updated concept
2024-02-09 Added frame folder and rocket assembly
2024-02-14 Updated fins and rocket assembly
2024-02-23 Added new avionics design
2024-02-23 Create RecoveryPlate23-24
2024-02-25 Modified tail cone and fin can. Update rocket assembly
2024-03-27 Updated fin mates on rocket assembly
2024-03-27 updated upper frame and assembly
2024-04-01 Updated part drawings and simulations
2024-04-02 Updated assembly
2024-04-14 Add files via upload
    Av-Bay v1
2024-06-25 Added fin alignment files
